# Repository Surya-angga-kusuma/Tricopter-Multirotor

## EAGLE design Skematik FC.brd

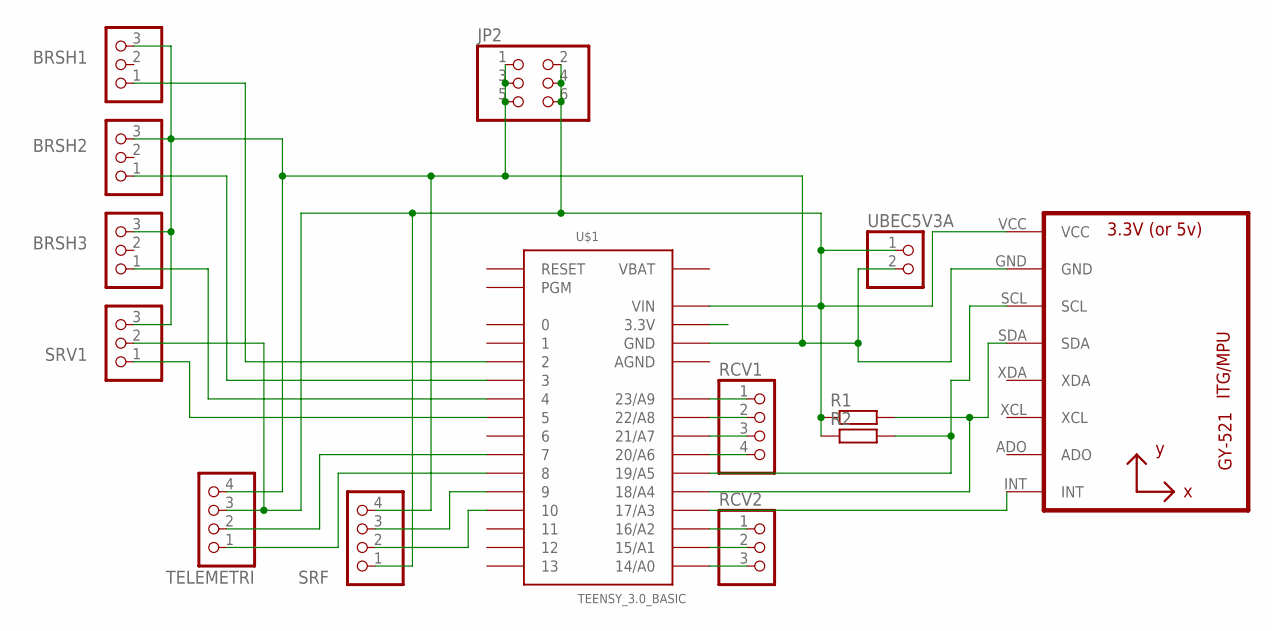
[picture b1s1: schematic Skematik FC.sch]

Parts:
BRSH1, BRSH3: PINHD-1X3; 1X03
BRSHL2: BRSH2; 1X03
JP2: PINHD-2X3; 2X03
R1, R2: R-EU_0207/7; 0207/7
RCV1: PINHD-1X4; 1X04
RCV2: PINHD-1X3; 1X03
SRF: PINHD-1X4; 1X04
SRV1: PINHD-1X3; 1X03
TELEMETRI: PINHD-1X4; 1X04
U1: GY-521MPU6050; GY-521
U$1: TEENSY_3.0_BASIC
UBEC5V3A: PINHD-1X2; 1X02

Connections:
AGND: U$1.AGND
unnamed: TELEMETRI.1, U$1.8
unnamed: R2.2, U1.SCL, U$1.19/A5
unnamed: R1.2, U1.SDA, U$1.18/A4
unnamed: U1.INT, U$1.17/A3
unnamed: BRSHL2.1, U$1.3
unnamed: TELEMETRI.2, U$1.7
unnamed: BRSH1.1, U$1.2
unnamed: BRSH3.1, U$1.4
unnamed: SRV1.1, U$1.5
unnamed: RCV1.1, U$1.23/A9
unnamed: RCV1.2, U$1.22/A8
unnamed: RCV1.3, U$1.21/A7
unnamed: RCV1.4, U$1.20/A6
unnamed: RCV2.1, U$1.16/A2
unnamed: RCV2.2, U$1.15/A1
unnamed: RCV2.3, U$1.14/A0
unnamed: SRF.3, U$1.9
unnamed: SRF.2, U$1.10
unnamed: BRSH1.3, BRSH3.3, BRSHL2.3, JP2.1, JP2.3, JP2.5, SRF.4, SRV1.3, TELEMETRI.4, U1.GND, U$1.GND, U$1.GND1 (GND), UBEC5V3A.2
unnamed: JP2.2, JP2.4, JP2.6, R1.1, R2.1, SRF.1, SRV1.2, TELEMETRI.3, U1.VCC, U$1.VIN, UBEC5V3A.1
unnamed: U$1.3.3V, U$1.3.3V1 (3.3V)
VBAT: U$1.VBAT

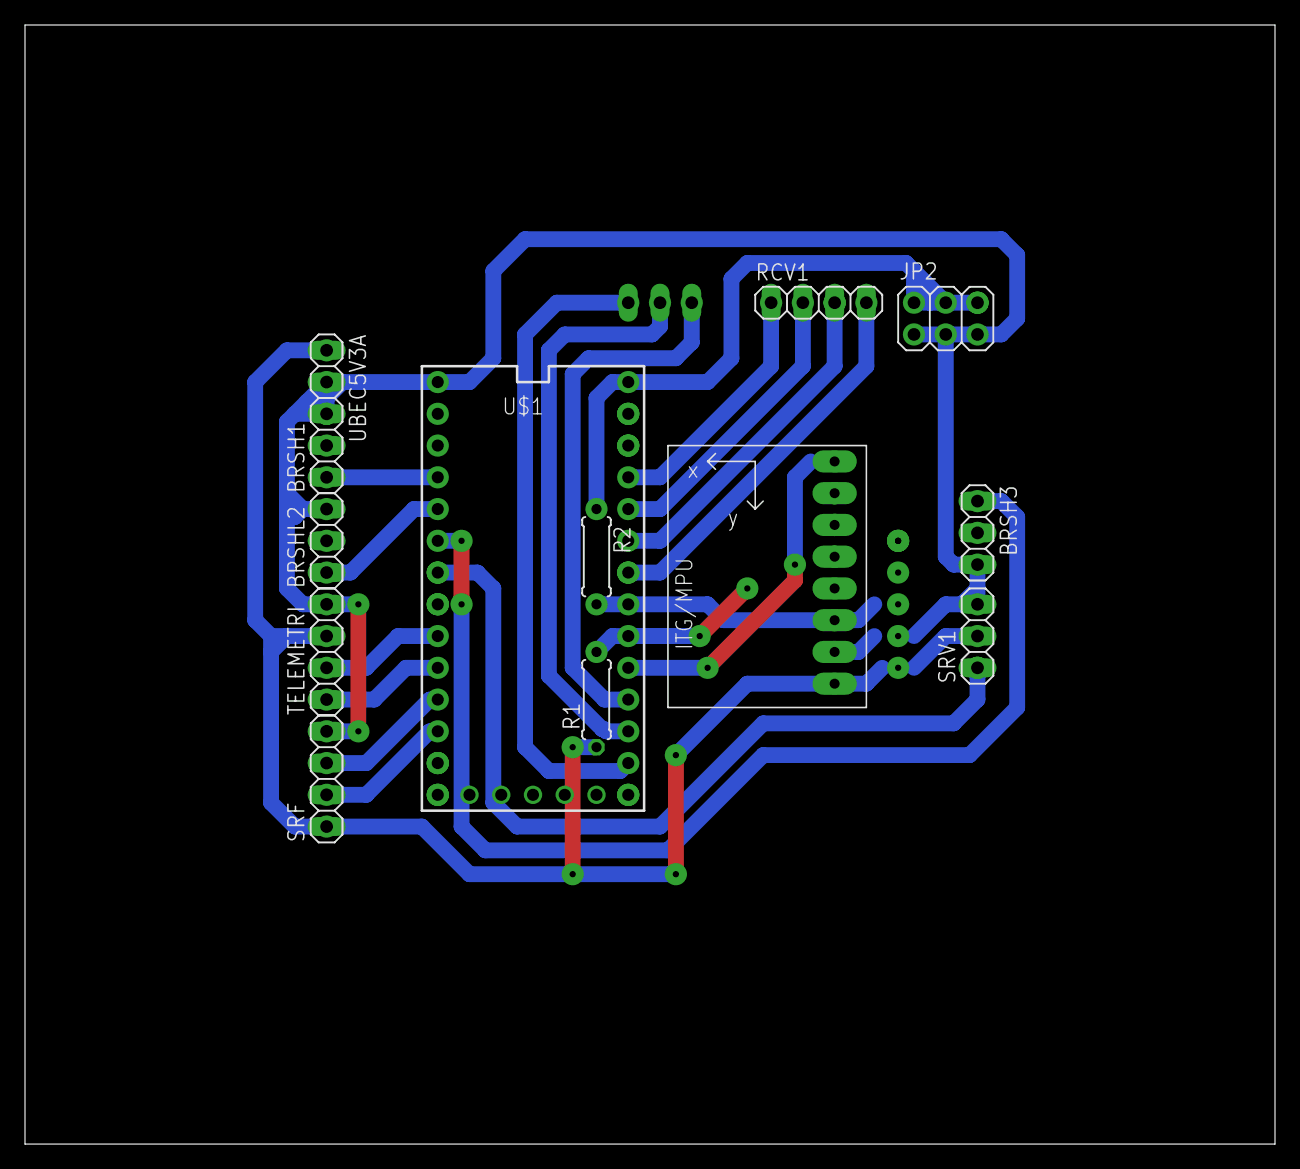
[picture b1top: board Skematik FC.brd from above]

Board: 2 copper layers, 100.0 x 89.5 mm, 14 parts (1 on the bottom side), 21 nets.
